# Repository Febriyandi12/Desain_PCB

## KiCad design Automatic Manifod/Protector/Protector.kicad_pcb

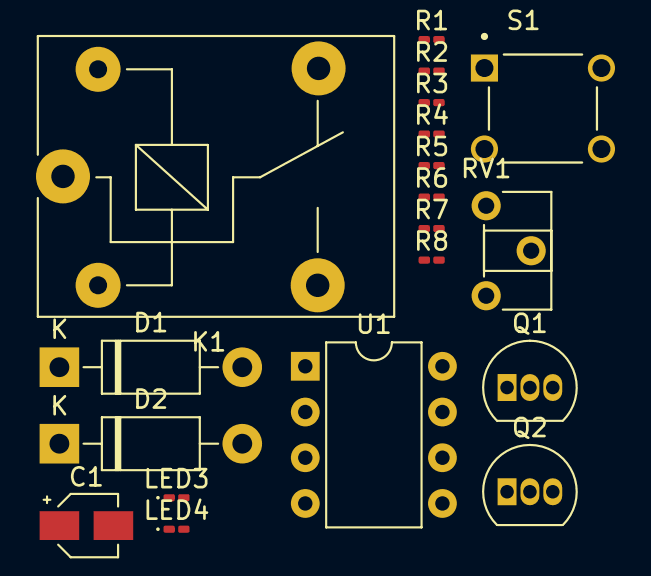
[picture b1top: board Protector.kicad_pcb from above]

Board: 2 copper layers, 19 parts (0 on the bottom side), 11 nets, no tracks yet.

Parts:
C1: 100uF 16V; CP_Elec_3x5.3
D1, D2: 1N4007; D_DO-41_SOD81_P10.16mm_Horizontal
K1: SRD-12VDC-SL-C; Relay_SPDT_SANYOU_SRD_Series_Form_C
LED3: ON; LED_0201_0603Metric_Pad0.64x0.40mm_HandSolder
LED4: TRIP; LED_0201_0603Metric_Pad0.64x0.40mm_HandSolder
Q1, Q2: BC547; TO-92_Inline
R1: 0.5 5W; R_0201_0603Metric_Pad0.64x0.40mm_HandSolder
R2, R7: 1K; R_0201_0603Metric_Pad0.64x0.40mm_HandSolder
R3, R4, R8: 10K; R_0201_0603Metric_Pad0.64x0.40mm_HandSolder
R5, R6: 2K2; R_0201_0603Metric_Pad0.64x0.40mm_HandSolder
RV1: 10K; Potentiometer_ACP_CA6-H2,5_Horizontal
S1: RESET; SW_TS02-66-95-BK-260-LCR-D
U1: NE555P; DIP-8_W7.62mm

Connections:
/12V: C1.1, D1.1 (K), K1.1, K1.5, LED3.2 (A), R3.1, R4.1, U1.8 (VCC)
/GND: C1.2, D2.2 (A), LED4.1 (K), Q1.3 (E), Q2.3 (E), R1.1, R1.2, R2.2, R8.2, RV1.1, S1.1, S1.2, U1.1 (GND), U1.6 (THR)
/VS: D2.1 (K), K1.4
unnamed: D1.2 (A), K1.2, Q2.1 (C)
unnamed: LED3.1 (K), R6.1
unnamed: LED4.2 (A), R5.2
unnamed: Q1.1 (C), R3.2, U1.2 (TR)
unnamed: Q2.2 (B), R7.2, R8.1
unnamed: R2.1, RV1.3
unnamed: R5.1, R6.2, R7.1, U1.3 (Q)
unnamed: R4.2, S1.3, S1.4, U1.4 (R)

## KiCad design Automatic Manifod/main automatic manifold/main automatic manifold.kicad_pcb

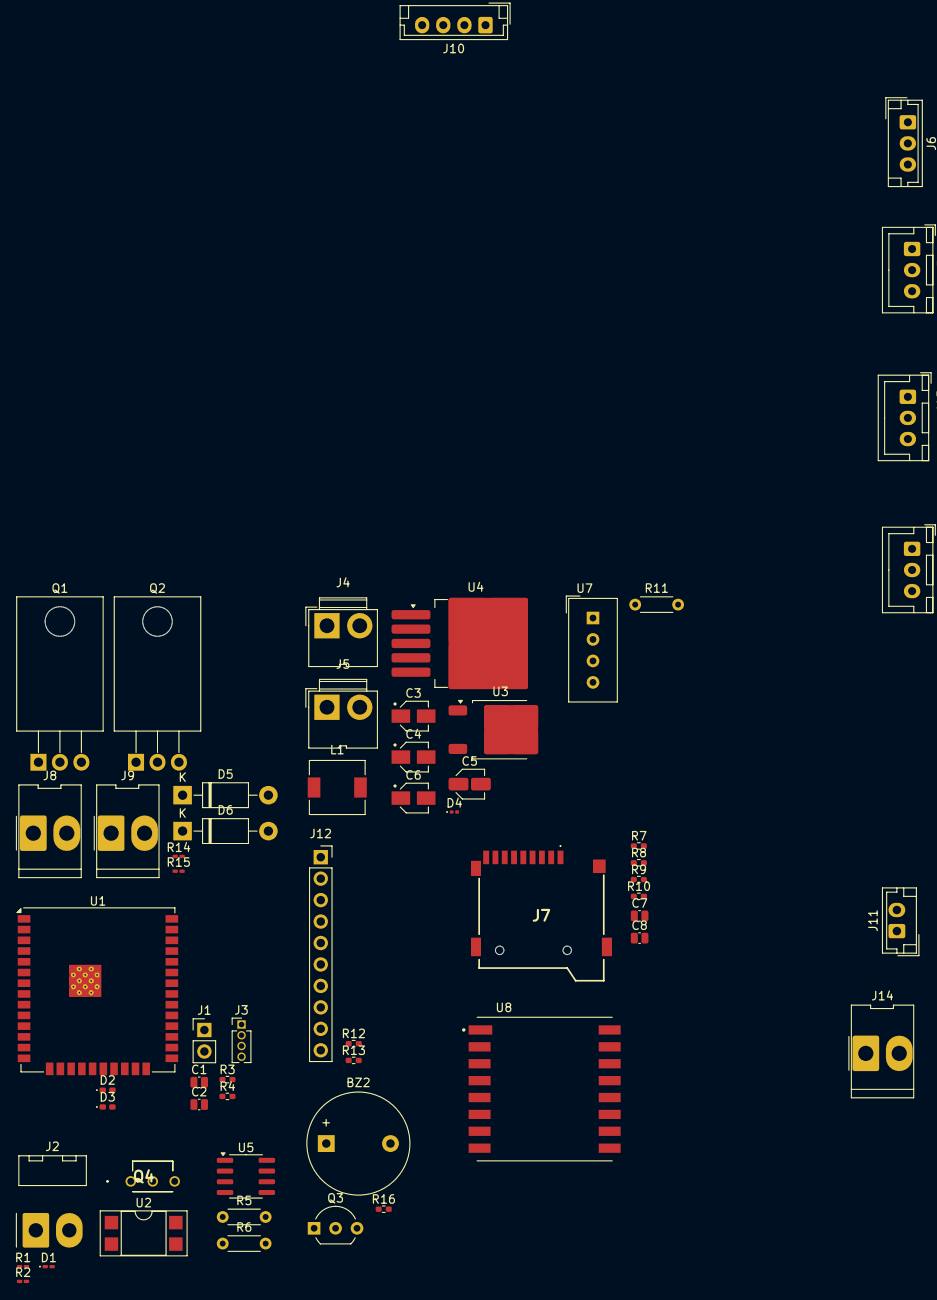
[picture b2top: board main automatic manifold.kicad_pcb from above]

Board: 2 copper layers, 59 parts (0 on the bottom side), 40 nets, no tracks yet.

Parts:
BZ2: Buzzer; Buzzer_12x9.5RM7.6
C1: 22uF; C_0504_1310Metric_Pad0.83x1.28mm_HandSolder
C2: 0.1uF; C_0504_1310Metric_Pad0.83x1.28mm_HandSolder
C3, C4: 10uF; CP_Elec_3x5.3
C5: 100uF; C_Elec_3x5.4
C6: 1000uF; CP_Elec_3x5.3
C7: 100nF; C_0504_1310Metric_Pad0.83x1.28mm_HandSolder
C8: 10uF; C_0504_1310Metric_Pad0.83x1.28mm_HandSolder
D1: LED; LED_0201_0603Metric_Pad0.64x0.40mm_HandSolder
D2: MERAH; LED_0402_1005Metric_Pad0.77x0.64mm_HandSolder
D3: BIRU; LED_0402_1005Metric_Pad0.77x0.64mm_HandSolder
D4: 1N5822; D_0201_0603Metric
D5, D6: 1N4007; D_DO-41_SOD81_P10.16mm_Horizontal
J1: Boot; PinHeader_1x02_P2.54mm_Vertical
J2: buzzer; Molex_KK-396_A-41792-0002_1x02_P3.96mm_Horizontal
J3: UART; PinHeader_1x04_P1.27mm_Vertical
J4, J5: Conn_01x02_Pin; JWT_A3963_1x02_P3.96mm_Vertical
J6: Input Flow; JST_EH_B3B-EH-A_1x03_P2.50mm_Vertical
J7: MSD-4-A; MSD4A
J8: Solenoid L; Molex_KK-396_5273-02A_1x02_P3.96mm_Vertical
J9: Solenoid R; Molex_KK-396_5273-02A_1x02_P3.96mm_Vertical
J10: Conn_01x04_Pin; JST_EH_B4B-EH-A_1x04_P2.50mm_Vertical
J11: IN 12V; JST_EH_B2B-EH-A_1x02_P2.50mm_Vertical
J12: ADS1015; PinSocket_1x10_P2.54mm_Vertical
J13: LEFT HIGH PREASURE; JST_XH_B3B-XH-A_1x03_P2.50mm_Vertical
J14: IN 24V; Molex_KK-396_5273-02A_1x02_P3.96mm_Vertical
J15: LOW PREASURE SENSOR; JST_XH_B3B-XH-A_1x03_P2.50mm_Vertical
J16: RIGHT PREASURE SENSOR; JST_XH_B3B-XH-A_1x03_P2.50mm_Vertical
L1: 100uh; L_6.3x6.3_H3
Q1, Q2: TIP120; TO-220-3_Horizontal_TabDown
Q3: BC547; TO-92_Inline_Wide
Q4: 2N5551-TA; 2N5551TA
R1: 1K; R_0201_0603Metric_Pad0.64x0.40mm_HandSolder
R2: 510; R_0201_0603Metric_Pad0.64x0.40mm_HandSolder
R3, R4: 1K; R_0402_1005Metric_Pad0.72x0.64mm_HandSolder
R5, R6: 1k8; R_Axial_DIN0204_L3.6mm_D1.6mm_P5.08mm_Horizontal
R7, R8, R9, R10, R12, R13: 10K; R_0402_1005Metric_Pad0.72x0.64mm_HandSolder
R11: 5K1; R_Axial_DIN0204_L3.6mm_D1.6mm_P5.08mm_Horizontal
R14, R15: 10K; R_0201_0603Metric_Pad0.64x0.40mm_HandSolder
R16: 1k; R_0402_1005Metric_Pad0.72x0.64mm_HandSolder
U1: ESP32-WROOM-32UE
U2: PC817; DIP-4_W7.62mm_SMDSocket_SmallPads
U3: LM1117DT-3.3; TO-252-2
U4: LM2576S-5; TO-263-5_TabPin3
U5: FM24C64B; SOIC-8_3.9x4.9mm_P1.27mm
U7: DHT11; Aosong_DHT11_5.5x12.0_P2.54mm
U8: RA-02_LORA; MODULE_RA-02_LORA

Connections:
+3.3V: C1.1, C2.1, C4.1, C7.1, C8.1, J3.1, J7.4 (VDD), J12.1, J12.5, R4.1, R5.1, R6.1, R7.1, R8.2, R9.2, R10.2, R12.1, R13.1, U1.2 (VDD), U3.2 (VO), U5.8 (VDD), U8.3 (3.3V)
+5V: BZ2.1 (+), C6.1, J4.1, J5.1, J6.1, J10.1, J16.3, L1.2, R11.1, U4.4 (FB), U7.1 (VDD)
+12V: C3.1, C5.1, D5.1 (K), D6.1 (K), J2.1, J4.2, J5.2, J8.2, J9.2, J11.1, J13.3, J14.1, J15.3, U2.4, U3.3 (VI), U4.1 (VIN)
/CLK: J7.5 (CLK), R9.1
/CS: J7.2 (CD/DAT3), R7.2, U1.29 (IO5), U8.15 (NSS)
/D2: R3.2, U1.24 (IO2)
/D4: R16.1, U1.26 (IO4)
/D12: R11.2, U1.14 (IO12), U7.2 (DATA)
/D13: R1.1, U1.16 (IO13)
/D14: J6.2, U1.13 (IO14)
/D15: U1.23 (IO15), U8.4 (RESET)
/D25: R14.1, U1.10 (IO25)
/D26: R15.1, U1.11 (IO26)
/D32: J12.7, J13.2, U1.8 (IO32)
/D33: U1.9 (IO33), U8.5 (DI00)
/D34: J12.8, J16.2, U1.6 (IO34)
/D35: J12.9, J15.2, U1.7 (IO35)
/MISO: J7.3 (CMD), R8.1, U1.31 (IO19), U8.13 (MISO)
/MOSI: J7.7 (DAT0), R10.1, U1.37 (IO23), U8.14 (MOSI)
/SCK: U1.30 (IO18), U8.12 (SCK)
/SCL: J12.3, R6.2, R12.2, U1.36 (IO22), U5.6 (SCL)
/SDA: J12.4, R5.2, R13.2, U1.33 (IO21), U5.5 (SDA)
GND: C1.2, C2.2, C3.2, C4.2, C5.2, C6.2, C7.2, C8.2, D1.1 (K), D2.1 (K), D3.1 (K), D4.2 (A), J1.2, J3.4, J6.3, J7.6 (VSS), J7.G1 (GND_1), J7.G2 (GND_2), J7.G3 (GND_3), J7.G4 (GND_4), J10.4, J11.2, J12.2, J13.1, J14.2, J15.1, J16.1, Q1.3 (E), Q2.3 (E), Q3.3 (E), Q4.3 (E), U1.1 (GND), U1.15 (GND), U1.38 (GND), U1.39 (GND), U3.1 (GND), U4.3 (GND), U4.5 (~ON/OFF), U5.1 (A0), U5.2 (A1), U5.3 (A2), U5.4 (VSS), U7.4 (GND), U8.1 (GND), U8.2 (GND), U8.9 (GND), U8.16 (GND)
unnamed: BZ2.2 (-), Q3.1 (C)
unnamed: D1.2 (A), U2.2
unnamed: D2.2 (A), R4.2
unnamed: D3.2 (A), R3.1
unnamed: D4.1 (K), L1.1, U4.2 (OUT)
unnamed: D5.2 (A), J8.1, Q1.2 (C)
unnamed: D6.2 (A), J9.1, Q2.2 (C)
unnamed: J1.1, U1.25 (IO0)
unnamed: J2.2, Q4.1 (C)
unnamed: J3.2, U1.35 (TXD0/IO1)
unnamed: J3.3, U1.34 (RXD0/IO3)
unnamed: Q1.1 (B), R14.2
unnamed: Q2.1 (B), R15.2
unnamed: Q3.2 (B), R16.2
unnamed: Q4.2 (B), R2.2
unnamed: R1.2, U2.1
unnamed: R2.1, U2.3

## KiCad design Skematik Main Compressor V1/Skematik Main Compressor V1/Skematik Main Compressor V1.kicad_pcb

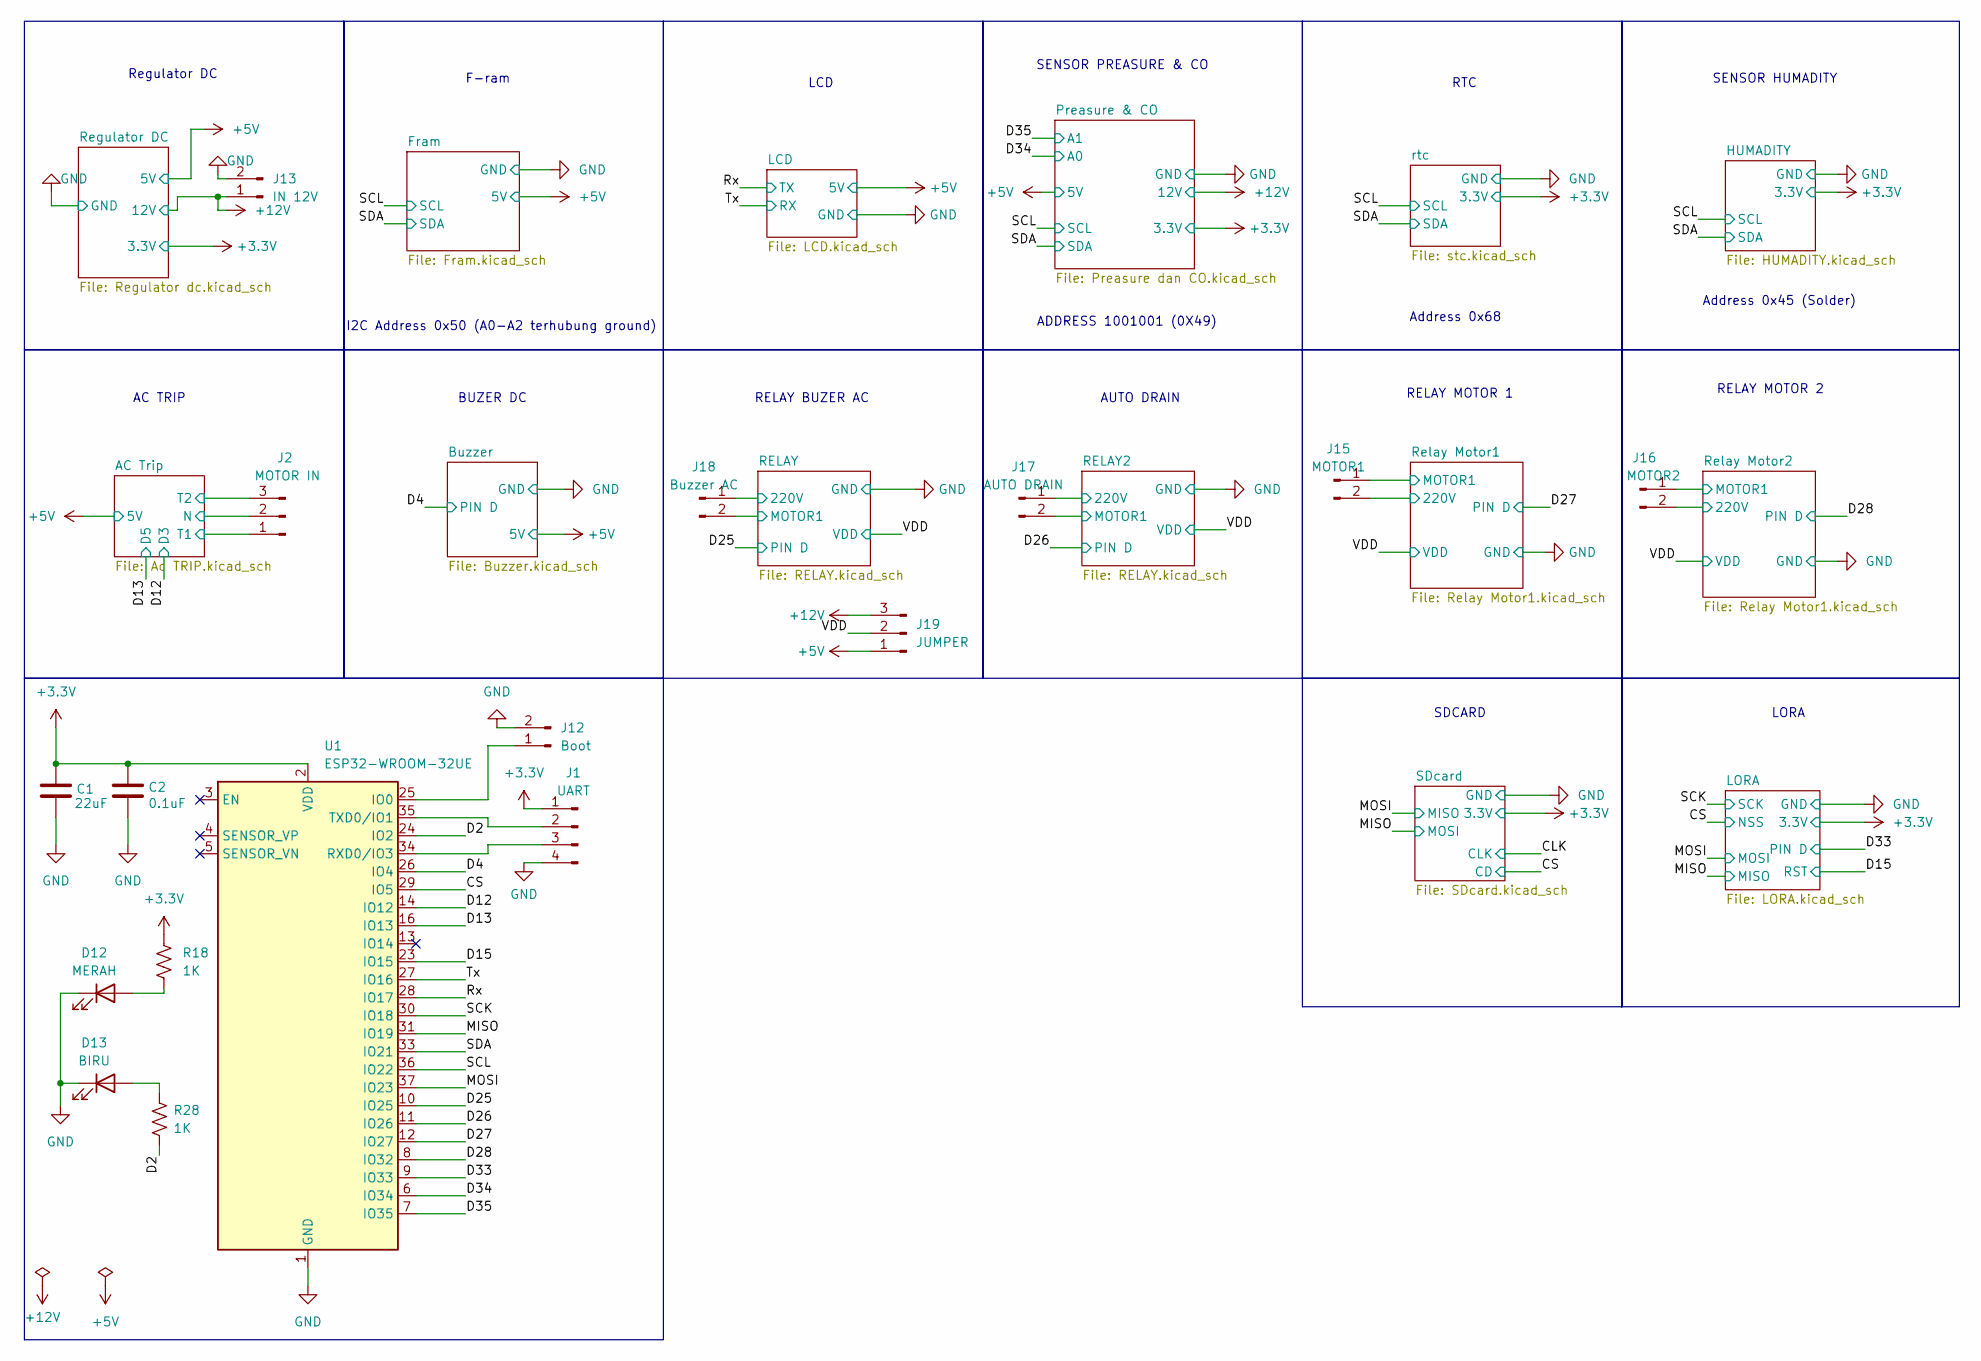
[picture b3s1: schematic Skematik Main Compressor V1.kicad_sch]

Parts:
C1: 22uF; C_0504_1310Metric_Pad0.83x1.28mm_HandSolder
C2: 0.1uF; C_0504_1310Metric_Pad0.83x1.28mm_HandSolder
D12: MERAH; LED_0402_1005Metric_Pad0.77x0.64mm_HandSolder
D13: BIRU; LED_0402_1005Metric_Pad0.77x0.64mm_HandSolder
J1: UART; PinHeader_1x04_P1.27mm_Vertical
J2: MOTOR IN; Molex_KK-396_A-41791-0003_1x03_P3.96mm_Vertical
J12: Boot; PinHeader_1x02_P2.54mm_Vertical
J13: IN 12V; Molex_KK-396_A-41791-0002_1x02_P3.96mm_Vertical
J15: MOTOR1; Molex_KK-396_A-41791-0002_1x02_P3.96mm_Vertical
J16: MOTOR2; Molex_KK-396_A-41791-0002_1x02_P3.96mm_Vertical
J17: AUTO DRAIN; Molex_KK-396_A-41791-0002_1x02_P3.96mm_Vertical
J18: Buzzer AC; Molex_KK-396_A-41791-0002_1x02_P3.96mm_Vertical
J19: JUMPER; PinHeader_1x03_P2.54mm_Vertical
R18, R28: 1K; R_0402_1005Metric_Pad0.72x0.64mm_HandSolder
U1: ESP32-WROOM-32UE

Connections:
+3.3V: C1.1, C2.1, J1.1, R18.1, U1.2 (VDD); also elsewhere on the board
+5V: J19.1; also elsewhere on the board
+12V: J13.1, J19.3; also elsewhere on the board
/AC Trip/N: J2.2; also elsewhere on the board
/AC Trip/T1: J2.1; also elsewhere on the board
/AC Trip/T2: J2.3; also elsewhere on the board
/CS: U1.29 (IO5); also elsewhere on the board
/D2: R28.2, U1.24 (IO2)
/D4: U1.26 (IO4); also elsewhere on the board
/D12: U1.14 (IO12); also elsewhere on the board
/D13: U1.16 (IO13); also elsewhere on the board
/D15: U1.23 (IO15); also elsewhere on the board
/D25: U1.10 (IO25); also elsewhere on the board
/D26: U1.11 (IO26); also elsewhere on the board
/D27: U1.12 (IO27); also elsewhere on the board
/D28: U1.8 (IO32); also elsewhere on the board
/D33: U1.9 (IO33); also elsewhere on the board
/D34: U1.6 (IO34); also elsewhere on the board
/D35: U1.7 (IO35); also elsewhere on the board
/MISO: U1.31 (IO19); also elsewhere on the board
/MOSI: U1.37 (IO23); also elsewhere on the board
/RELAY2/220V: J17.1; also elsewhere on the board
/RELAY2/MOTOR1: J17.2; also elsewhere on the board
/RELAY/220V: J18.1; also elsewhere on the board
/RELAY/MOTOR1: J18.2; also elsewhere on the board
/Relay Motor1/220V: J15.2; also elsewhere on the board
/Relay Motor1/MOTOR1: J15.1; also elsewhere on the board
/Relay Motor2/220V: J16.2; also elsewhere on the board
/Relay Motor2/MOTOR1: J16.1; also elsewhere on the board
/Rx: U1.28 (IO17); also elsewhere on the board
/SCK: U1.30 (IO18); also elsewhere on the board
/SCL: U1.36 (IO22); also elsewhere on the board
/SDA: U1.33 (IO21); also elsewhere on the board
/Tx: U1.27 (IO16); also elsewhere on the board
/VDD: J19.2; also elsewhere on the board
GND: C1.2, C2.2, D12.1 (K), D13.1 (K), J1.4, J12.2, J13.2, U1.1 (GND), U1.15 (GND), U1.38 (GND), U1.39 (GND); also elsewhere on the board
unnamed: D12.2 (A), R18.2
unnamed: D13.2 (A), R28.1
unnamed: J1.2, U1.35 (TXD0/IO1)
unnamed: J1.3, U1.34 (RXD0/IO3)
unnamed: J12.1, U1.25 (IO0)

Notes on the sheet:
RELAY MOTOR 1
ADDRESS 1001001 (0X49)
LORA
BUZER DC
Address 0x68
SENSOR PREASURE & CO
F-ram
Address 0x45 (Solder)
RTC
LCD
AUTO DRAIN
RELAY BUZER AC
AC TRIP
SDCARD
Regulator DC
SENSOR HUMADITY
I2C Address 0x50 (A0-A2 terhubung ground)
RELAY MOTOR 2

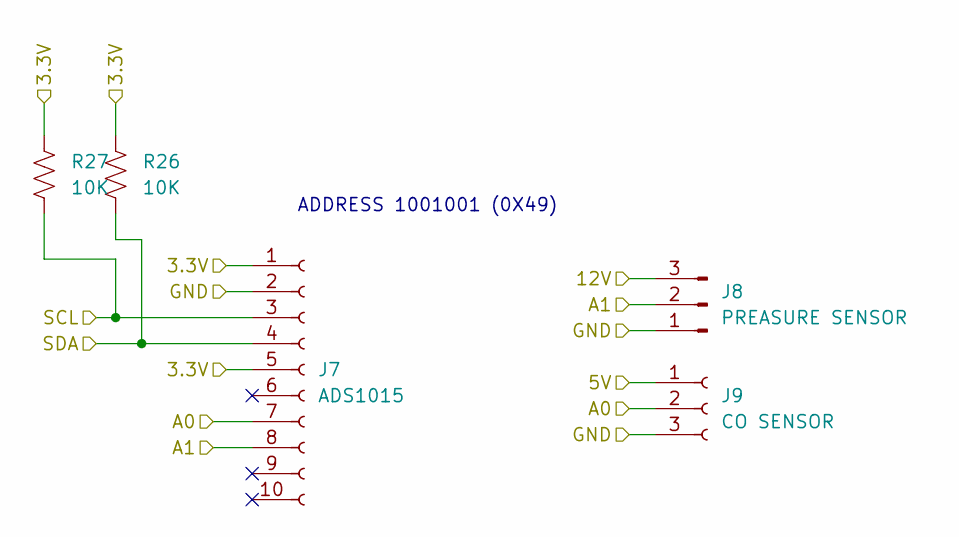
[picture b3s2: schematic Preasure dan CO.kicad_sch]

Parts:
J7: ADS1015; PinSocket_1x10_P2.54mm_Vertical
J8: PREASURE SENSOR; JST_XH_B3B-XH-A_1x03_P2.50mm_Vertical
J9: CO SENSOR; JST_XA_B03B-XASK-1_1x03_P2.50mm_Vertical
R26, R27: 10K; R_0402_1005Metric_Pad0.72x0.64mm_HandSolder

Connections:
+3.3V: J7.1, J7.5, R26.1, R27.1; also elsewhere on the board
+5V: J9.1; also elsewhere on the board
+12V: J8.3; also elsewhere on the board
/D34: J7.7, J9.2; also elsewhere on the board
/D35: J7.8, J8.2; also elsewhere on the board
/SCL: J7.3, R27.2; also elsewhere on the board
/SDA: J7.4, R26.2; also elsewhere on the board
GND: J7.2, J8.1, J9.3; also elsewhere on the board

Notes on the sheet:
ADDRESS 1001001 (0X49)

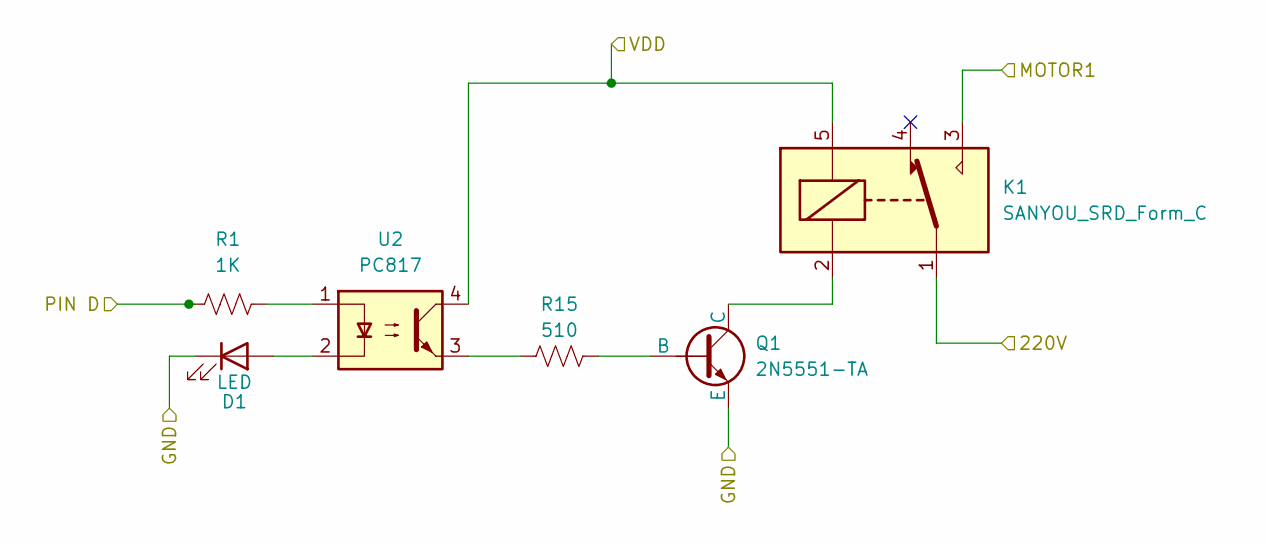
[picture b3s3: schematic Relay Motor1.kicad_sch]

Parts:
D1: LED; LED_0805_2012Metric_Pad1.15x1.40mm_HandSolder
K1: SANYOU_SRD_Form_C; Relay_SPDT_SANYOU_SRD_Series_Form_C
Q1: 2N5551-TA; TO-92_Inline_Wide
R1: 1K; R_0402_1005Metric_Pad0.72x0.64mm_HandSolder
R15: 510; R_0402_1005Metric_Pad0.72x0.64mm_HandSolder
U2: PC817; DIP-4_W7.62mm

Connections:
/D27: R1.1; also elsewhere on the board
/Relay Motor1/220V: K1.1; also elsewhere on the board
/Relay Motor1/MOTOR1: K1.3; also elsewhere on the board
/VDD: K1.5, U2.4; also elsewhere on the board
GND: D1.1 (K), Q1.3 (E); also elsewhere on the board
unnamed: D1.2 (A), U2.2
unnamed: Q1.2 (B), R15.2
unnamed: K1.2, Q1.1 (C)
unnamed: R1.2, U2.1
unnamed: R15.1, U2.3

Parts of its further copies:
D4: LED; LED_0805_2012Metric_Pad1.15x1.40mm_HandSolder
K3: SANYOU_SRD_Form_C; Relay_SPDT_SANYOU_SRD_Series_Form_C
Q2: 2N5551-TA; TO-92_Inline_Wide
R2: 1K; R_0402_1005Metric_Pad0.72x0.64mm_HandSolder
R16: 510; R_0402_1005Metric_Pad0.72x0.64mm_HandSolder
U10: PC817; DIP-4_W7.62mm

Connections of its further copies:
/D28: R2.1; also elsewhere on the board
/Relay Motor2/220V: K3.1; also elsewhere on the board
/Relay Motor2/MOTOR1: K3.3; also elsewhere on the board
/VDD: K3.5, U10.4; also elsewhere on the board
GND: D4.1 (K), Q2.3 (E); also elsewhere on the board
unnamed: D4.2 (A), U10.2
unnamed: Q2.2 (B), R16.2
unnamed: K3.2, Q2.1 (C)
unnamed: R2.2, U10.1
unnamed: R16.1, U10.3

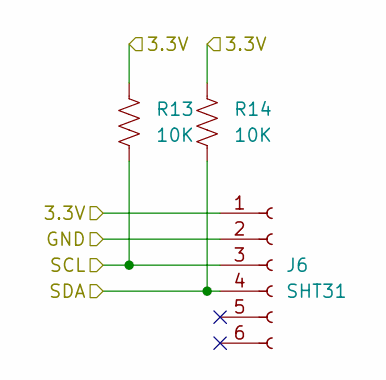
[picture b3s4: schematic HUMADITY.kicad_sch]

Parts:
J6: SHT31; PinHeader_1x06_P2.54mm_Vertical
R13, R14: 10K; R_0402_1005Metric_Pad0.72x0.64mm_HandSolder

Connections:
+3.3V: J6.1, R13.1, R14.1; also elsewhere on the board
/SCL: J6.3, R13.2; also elsewhere on the board
/SDA: J6.4, R14.2; also elsewhere on the board
GND: J6.2; also elsewhere on the board

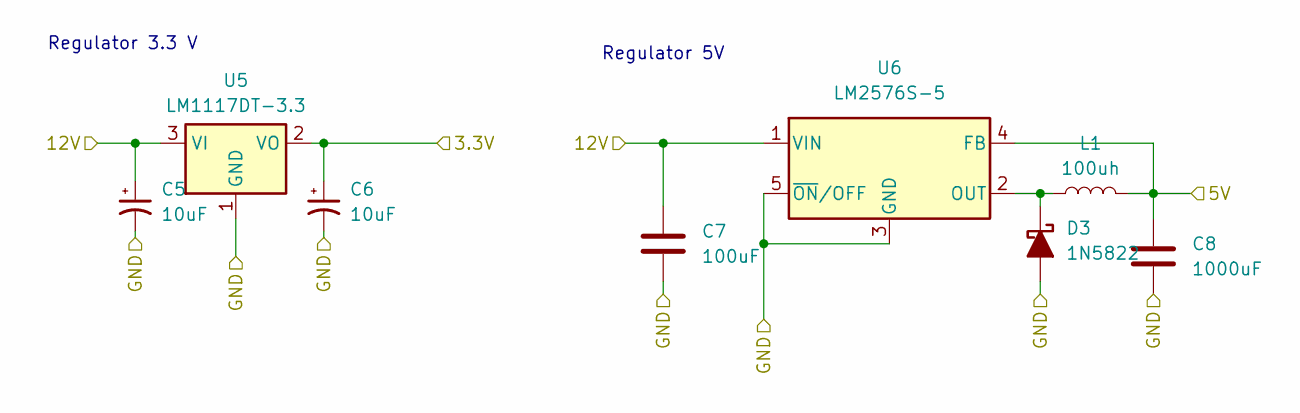
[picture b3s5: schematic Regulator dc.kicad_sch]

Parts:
C5, C6: 10uF; CP_Elec_3x5.3
C7: 100uF; C_Elec_3x5.4
C8: 1000uF; CP_Elec_3x5.3
D3: 1N5822; D_0201_0603Metric
L1: 100uh; L_6.3x6.3_H3
U5: LM1117DT-3.3; TO-252-2
U6: LM2576S-5; TO-263-5_TabPin3

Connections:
+3.3V: C6.1, U5.2 (VO); also elsewhere on the board
+5V: C8.1, L1.2, U6.4 (FB); also elsewhere on the board
+12V: C5.1, C7.1, U5.3 (VI), U6.1 (VIN); also elsewhere on the board
GND: C5.2, C6.2, C7.2, C8.2, D3.2 (A), U5.1 (GND), U6.3 (GND), U6.5 (~ON/OFF); also elsewhere on the board
unnamed: D3.1 (K), L1.1, U6.2 (OUT)

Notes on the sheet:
Regulator 5V
Regulator 3.3 V

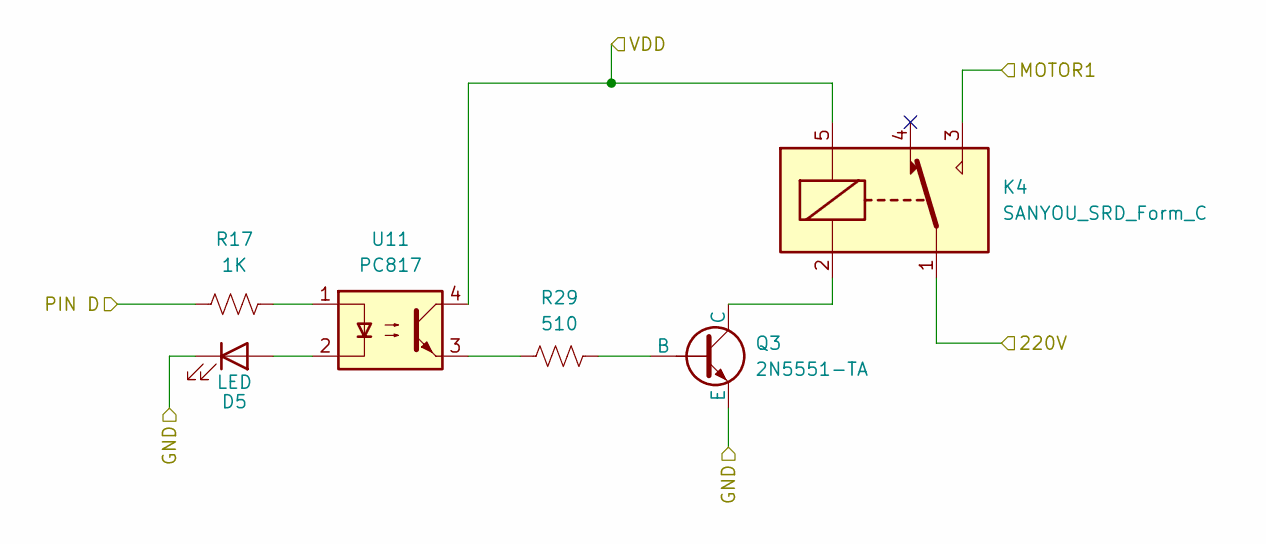
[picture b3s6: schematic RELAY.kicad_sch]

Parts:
D5: LED; LED_0805_2012Metric_Pad1.15x1.40mm_HandSolder
K4: SANYOU_SRD_Form_C; Relay_SPDT_SANYOU_SRD_Series_Form_C
Q3: 2N5551-TA; TO-92_Inline_Wide
R17: 1K; R_0402_1005Metric_Pad0.72x0.64mm_HandSolder
R29: 510; R_0402_1005Metric_Pad0.72x0.64mm_HandSolder
U11: PC817; DIP-4_W7.62mm

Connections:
/D26: R17.1; also elsewhere on the board
/RELAY2/220V: K4.1; also elsewhere on the board
/RELAY2/MOTOR1: K4.3; also elsewhere on the board
/VDD: K4.5, U11.4; also elsewhere on the board
GND: D5.1 (K), Q3.3 (E); also elsewhere on the board
unnamed: D5.2 (A), U11.2
unnamed: R17.2, U11.1
unnamed: R29.1, U11.3

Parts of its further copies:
D2: LED; LED_0805_2012Metric_Pad1.15x1.40mm_HandSolder
K2: SANYOU_SRD_Form_C; Relay_SPDT_SANYOU_SRD_Series_Form_C
Q4: 2N5551-TA; TO-92_Inline_Wide
R11: 1K; R_0402_1005Metric_Pad0.72x0.64mm_HandSolder
R12: 510; R_0402_1005Metric_Pad0.72x0.64mm_HandSolder
U4: PC817; DIP-4_W7.62mm

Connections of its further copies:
/D25: R11.1; also elsewhere on the board
/RELAY/220V: K2.1; also elsewhere on the board
/RELAY/MOTOR1: K2.3; also elsewhere on the board
/VDD: K2.5, U4.4; also elsewhere on the board
GND: D2.1 (K), Q4.3 (E); also elsewhere on the board
unnamed: D2.2 (A), U4.2
unnamed: R11.2, U4.1
unnamed: R12.1, U4.3

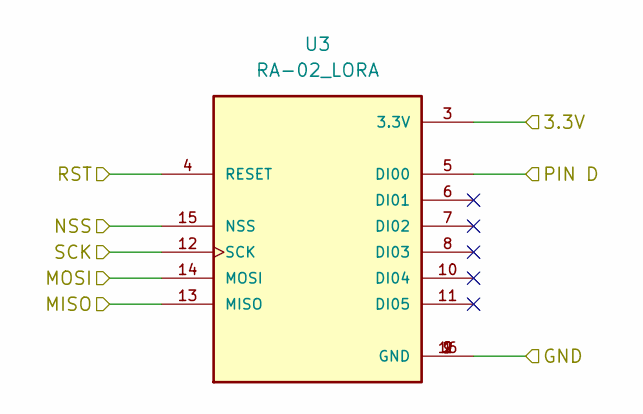
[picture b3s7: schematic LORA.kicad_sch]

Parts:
U3: RA-02_LORA; Ai-Thinker-Ra-01-LoRa; PARTREV 2018/03/02

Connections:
+3.3V: U3.3 (3.3V); also elsewhere on the board
/CS: U3.15 (NSS); also elsewhere on the board
/D15: U3.4 (RESET); also elsewhere on the board
/D33: U3.5 (DI00); also elsewhere on the board
/MISO: U3.13 (MISO); also elsewhere on the board
/MOSI: U3.14 (MOSI); also elsewhere on the board
/SCK: U3.12 (SCK); also elsewhere on the board
GND: U3.1 (GND), U3.2 (GND), U3.9 (GND), U3.16 (GND); also elsewhere on the board

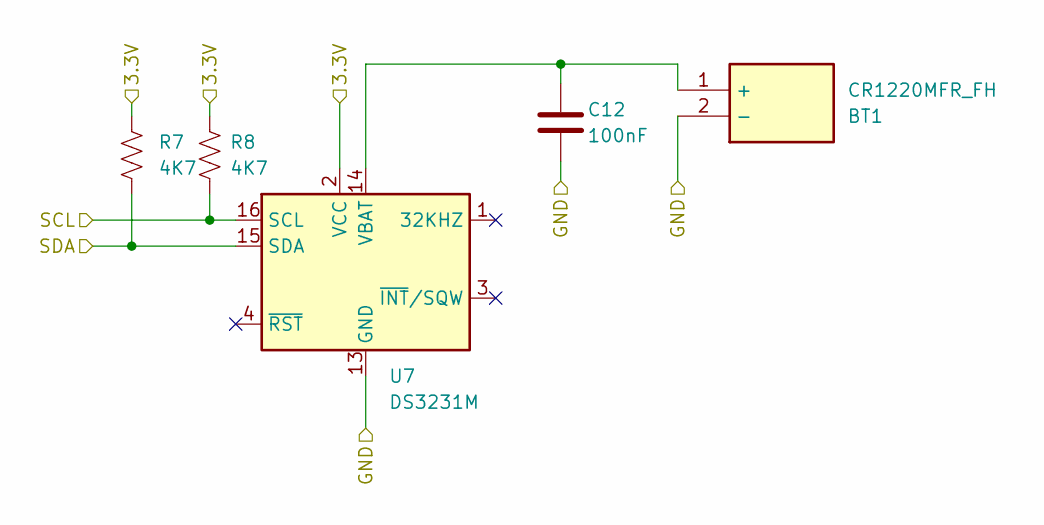
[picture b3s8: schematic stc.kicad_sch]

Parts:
BT1: CR1220MFR_FH; CR1220-SMD; Mouser Part Number 614-CR1220MFR-FH
C12: 100nF; C_0402_1005Metric_Pad0.74x0.62mm_HandSolder
R7, R8: 4K7; R_0402_1005Metric_Pad0.72x0.64mm_HandSolder
U7: DS3231M; SOIC-16W_7.5x10.3mm_P1.27mm

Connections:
+3.3V: R7.1, R8.1, U7.2 (VCC); also elsewhere on the board
/SCL: R8.2, U7.16 (SCL); also elsewhere on the board
/SDA: R7.2, U7.15 (SDA); also elsewhere on the board
GND: BT1.2 (-), C12.2, U7.5 (GND), U7.6 (GND), U7.7 (GND), U7.8 (GND), U7.9 (GND), U7.10 (GND), U7.11 (GND), U7.12 (GND), U7.13 (GND); also elsewhere on the board
unnamed: BT1.1 (+), C12.1, U7.14 (VBAT)

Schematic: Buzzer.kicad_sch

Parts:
BZ1: Buzzer; Buzzer_12x9.5RM7.6
Q5: BC547; TO-92_Inline_Wide
R19: 1k; R_0402_1005Metric_Pad0.72x0.64mm_HandSolder

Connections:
+5V: BZ1.1 (+); also elsewhere on the board
/D4: R19.1; also elsewhere on the board
GND: Q5.3 (E); also elsewhere on the board
unnamed: BZ1.2 (-), Q5.1 (C)
unnamed: Q5.2 (B), R19.2

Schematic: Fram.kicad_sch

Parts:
R9: 1k8; R_0402_1005Metric_Pad0.72x0.64mm_HandSolder
R10: 1k8; R_Axial_DIN0204_L3.6mm_D1.6mm_P5.08mm_Horizontal
U9: FM24C64B; SOIC-8_3.9x4.9mm_P1.27mm

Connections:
+5V: R9.1, R10.1, U9.8 (VDD); also elsewhere on the board
/SCL: R10.2, U9.6 (SCL); also elsewhere on the board
/SDA: R9.2, U9.5 (SDA); also elsewhere on the board
GND: U9.1 (A0), U9.2 (A1), U9.3 (A2), U9.4 (VSS); also elsewhere on the board

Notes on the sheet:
I2C Address 0x50 (A0-A2 terhubung ground)
FRAM (Ferroelectric RAM)

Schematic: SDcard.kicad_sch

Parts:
C3: 100nF; C_0504_1310Metric_Pad0.83x1.28mm_HandSolder
C4: 10uF; C_0504_1310Metric_Pad0.83x1.28mm_HandSolder
J3: MSD-4-A; CUI_MSD-4-A; Mouser Part Number 179-MSD-4-A
R3, R4, R5, R6: 10K; R_0402_1005Metric_Pad0.72x0.64mm_HandSolder

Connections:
+3.3V: C3.1, C4.1, J3.4 (VDD), R3.1, R4.2, R5.2, R6.2; also elsewhere on the board
/CLK: J3.5 (CLK), R5.1
/CS: J3.2 (CD/DAT3), R3.2; also elsewhere on the board
/MISO: J3.3 (CMD), R4.1; also elsewhere on the board
/MOSI: J3.7 (DAT0), R6.1; also elsewhere on the board
GND: C3.2, C4.2, J3.6 (VSS), J3.G1 (GND_1), J3.G2 (GND_2), J3.G3 (GND_3), J3.G4 (GND_4); also elsewhere on the board

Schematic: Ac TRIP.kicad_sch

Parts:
C9, C10: C_Polarized_US; CP_Elec_3x5.3
D6, D7: MB6S; TO-269AA
D8, D9: D_Schottky_Small_Filled; D_0201_0603Metric_Pad0.64x0.40mm_HandSolder
D10: TRIP 1; LED_0201_0603Metric_Pad0.64x0.40mm_HandSolder
D11: TRIP 2; LED_0201_0603Metric_Pad0.64x0.40mm_HandSolder
R20, R21: 150K; R_Axial_DIN0204_L3.6mm_D1.6mm_P5.08mm_Horizontal
R22, R23, R24, R25: 10k; R_Axial_DIN0204_L3.6mm_D1.6mm_P5.08mm_Horizontal
U12, U13: PC817; DIP-4_W7.62mm

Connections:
+5V: R22.2, R24.2; also elsewhere on the board
/AC Trip/N: D6.1, D7.1; also elsewhere on the board
/AC Trip/T1: R20.2; also elsewhere on the board
/AC Trip/T2: R21.2; also elsewhere on the board
/D12: R22.1, R23.1, U12.4; also elsewhere on the board
/D13: R24.1, R25.1, U13.4; also elsewhere on the board
GND: R23.2, R25.2, U12.3, U13.3; also elsewhere on the board
unnamed: C9.2, D6.4 (-), D8.2 (A), U12.2
unnamed: D6.2, R20.1
unnamed: C10.2, D7.4 (-), D9.2 (A), U13.2
unnamed: D7.2, R21.1
unnamed: C9.1, D6.3 (+), D8.1 (K), D10.2 (A)
unnamed: D10.1 (K), U12.1
unnamed: C10.1, D7.3 (+), D9.1 (K), D11.2 (A)
unnamed: D11.1 (K), U13.1

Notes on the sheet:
Input AC / Trip

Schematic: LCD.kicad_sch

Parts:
J4: Conn_01x04_Pin; JST_EH_B4B-EH-A_1x04_P2.50mm_Vertical

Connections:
+5V: J4.1; also elsewhere on the board
/Rx: J4.2; also elsewhere on the board
/Tx: J4.3; also elsewhere on the board
GND: J4.4; also elsewhere on the board

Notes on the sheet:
DISPLAY

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
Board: 2 copper layers, 92 parts (0 on the bottom side), 74 nets, no tracks yet.

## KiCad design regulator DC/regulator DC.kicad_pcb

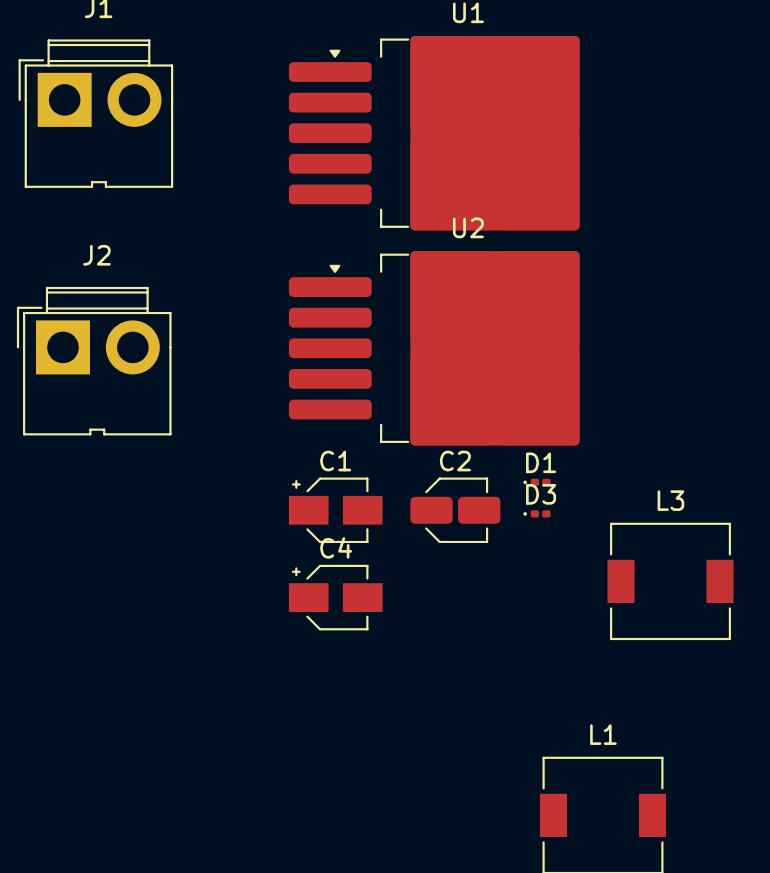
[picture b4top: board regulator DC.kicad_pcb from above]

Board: 2 copper layers, 11 parts (0 on the bottom side), 5 nets, no tracks yet.

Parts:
C1: 470uF 16V; CP_Elec_3x5.3
C2: 100uF; C_Elec_3x5.4
C4: 1000uF; CP_Elec_3x5.3
D1: 1n5822; D_0201_0603Metric
D3: 1N5822; D_0201_0603Metric
J1, J2: Conn_01x02_Pin; JWT_A3963_1x02_P3.96mm_Vertical
L1: 100uH; L_6.3x6.3_H3
L3: 100uh; L_6.3x6.3_H3
U1, U2: LM2576S-5; TO-263-5_TabPin3

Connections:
5V: C1.1, C4.1, J1.1, J2.1, L1.2, L3.2, U1.4 (FB), U2.4 (FB)
12V: C2.1, J1.2, J2.2, U1.1 (VIN), U2.1 (VIN)
GND: C1.2, C2.2, C4.2, D1.2 (A), D3.2 (A), U1.3 (GND), U1.5 (~ON/OFF), U2.3 (GND), U2.5 (~ON/OFF)
unnamed: D1.1 (K), L1.1, U1.2 (OUT)
unnamed: D3.1 (K), L3.1, U2.2 (OUT)

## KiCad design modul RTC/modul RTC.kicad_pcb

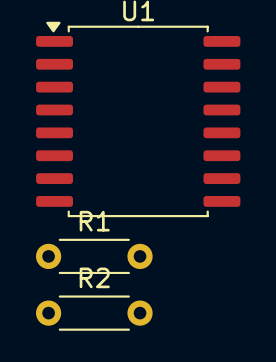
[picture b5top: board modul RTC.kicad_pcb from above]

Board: 2 copper layers, 3 parts (0 on the bottom side), 4 nets, no tracks yet.

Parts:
R1, R2: 4K7; R_Axial_DIN0204_L3.6mm_D1.6mm_P5.08mm_Horizontal
U1: DS3231M; SOIC-16W_7.5x10.3mm_P1.27mm

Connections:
GNDREF: U1.5 (GND), U1.6 (GND), U1.7 (GND), U1.8 (GND), U1.9 (GND), U1.10 (GND), U1.11 (GND), U1.12 (GND), U1.13 (GND)
unnamed: R2.2, U1.16 (SCL)
unnamed: R1.2, U1.15 (SDA)
SCL: R1.1, R2.1, U1.2 (VCC)

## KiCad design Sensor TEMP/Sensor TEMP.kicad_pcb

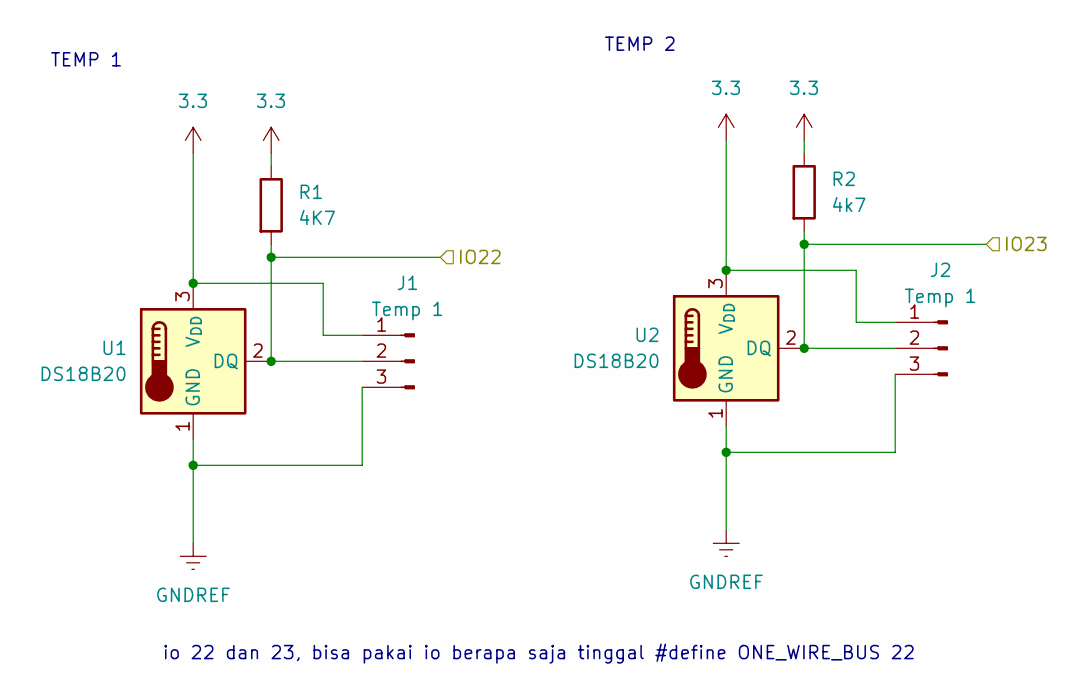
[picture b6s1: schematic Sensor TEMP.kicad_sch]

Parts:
J1, J2: Temp 1; JST_JWPF_B03B-JWPF-SK-R_1x03_P2.00mm_Vertical
R1: 4K7; R_Axial_DIN0204_L3.6mm_D1.6mm_P5.08mm_Horizontal
R2: 4k7; R_Axial_DIN0204_L3.6mm_D1.6mm_P5.08mm_Horizontal
U1, U2: DS18B20; TO-92_Inline

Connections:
3.3: J1.1, J2.1, R1.1, R2.1, U1.3 (V_{DD}), U2.3 (V_{DD})
GNDREF: J1.3, J2.3, U1.1 (GND), U2.1 (GND)
GPIo?: J1.2, J2.2, R1.2, R2.2, U1.2 (DQ), U2.2 (DQ)

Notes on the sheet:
TEMP 2
TEMP 1
io 22 dan 23, bisa pakai io berapa saja tinggal #define ONE_WIRE_BUS 22

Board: 2 copper layers, 6 parts (0 on the bottom side), 3 nets, no tracks yet.

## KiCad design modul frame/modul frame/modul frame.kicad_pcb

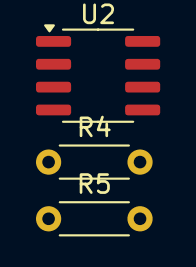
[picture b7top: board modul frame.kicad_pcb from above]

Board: 2 copper layers, 3 parts (0 on the bottom side), 4 nets, no tracks yet.

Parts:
R4, R5: 1k8; R_Axial_DIN0204_L3.6mm_D1.6mm_P5.08mm_Horizontal
U2: FM24C64B; SOIC-8_3.9x4.9mm_P1.27mm

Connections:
GND: U2.1 (A0), U2.2 (A1), U2.3 (A2), U2.4 (VSS)
unnamed: R5.2, U2.6 (SCL)
unnamed: R4.2, U2.5 (SDA)
SCL: R4.1, R5.1, U2.8 (VDD)

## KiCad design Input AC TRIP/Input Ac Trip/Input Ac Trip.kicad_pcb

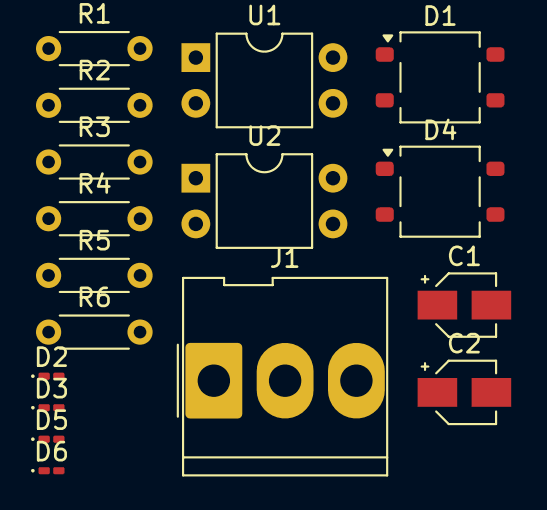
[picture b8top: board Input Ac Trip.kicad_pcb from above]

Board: 2 copper layers, 17 parts (0 on the bottom side), 15 nets, no tracks yet.

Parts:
C1, C2: C_Polarized_US; CP_Elec_3x5.3
D1, D4: MB6S; TO-269AA
D2, D5: D_Schottky_Small_Filled; D_0201_0603Metric_Pad0.64x0.40mm_HandSolder
D3: TRIP 1; LED_0201_0603Metric_Pad0.64x0.40mm_HandSolder
D6: TRIP 2; LED_0201_0603Metric_Pad0.64x0.40mm_HandSolder
J1: Conn_01x03_Pin; Molex_KK-396_5273-03A_1x03_P3.96mm_Vertical
R1, R4: 150K; R_Axial_DIN0204_L3.6mm_D1.6mm_P5.08mm_Horizontal
R2, R3, R5, R6: 10k; R_Axial_DIN0204_L3.6mm_D1.6mm_P5.08mm_Horizontal
U1, U2: PC817; DIP-4_W7.62mm

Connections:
5v: R2.2, R5.2
D3: R2.1, R3.1, U1.4
D5: R5.1, R6.1, U2.4
GND: R3.2, R6.2, U1.3, U2.3
unnamed: C1.1, D1.3 (+), D2.1 (K), D3.2 (A)
unnamed: C1.2, D1.4 (-), D2.2 (A), U1.2
unnamed: D1.2, R1.1
unnamed: D3.1 (K), U1.1
unnamed: C2.1, D4.3 (+), D5.1 (K), D6.2 (A)
unnamed: C2.2, D4.4 (-), D5.2 (A), U2.2
unnamed: D4.2, R4.1
unnamed: D6.1 (K), U2.1
unnamed: J1.1, R1.2
unnamed: D1.1, D4.1, J1.2
unnamed: J1.3, R4.2

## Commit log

2024-07-25 Skematik PCB
2024-07-26 menambahkan skematik
2024-07-26 Update Main
2024-07-27 Penambahan Skematik Main Compressor V1
2024-07-27 Perubahan skematik main dan tambahan dokumentasi pin
2024-07-27 update Main Compressor
2024-07-27 hapus file ganda pada main
2024-07-27 no message
2024-07-29 Update baru skematik main
2024-07-29 menghapus file tidak perlu
2024-07-30 Tambah skematik main automatic manifold
2024-07-30 menambahkan library
2024-08-07 test
